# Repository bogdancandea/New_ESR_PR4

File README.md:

# New_ESR_PR4
A redesigned PCB for the original ESR-PR4 ESR meter

Back in 2023, my ESR-PR4 broke due to an error (I measured a charged capacitor). My first thought was: oh well, it served me well until now—I'll just get another one. Identical.
However, over the years, the manufacturer had stopped production, and even the website had disappeared.

With some information from specialized forums and with the help of https://web.archive.org, I managed to access an archived version of the website that used to sell the product:

https://web.archive.org/web/20180327142201/http://x-roast.home.ro/

At that time, the author had published both the schematic and the software written for the microcontroller. So I was able to repair my device by replacing and reprogramming the microcontroller.

That’s when I got the idea to republish the information. Since the original information did not include the PCB, I designed a PCB version so that electronics enthusiasts could build the device themselves.

The author of the schematic and the software is unknown to me. I am using and republishing this information because it was publicly available at x-roast.home.ro. I have no commercial interest whatsoever.

There is a mismatch between the original schematic and the HEX file: pins 10 and 11 of the microcontroller are swapped.
The first unit I built had a few errors, including the swapped pins 10 and 11, which were fixed by cutting PCB traces and soldering wires.

The published version has already been corrected.

A new, smaller PCB version is currently in development, which I will publish only after I have had the chance to test it.

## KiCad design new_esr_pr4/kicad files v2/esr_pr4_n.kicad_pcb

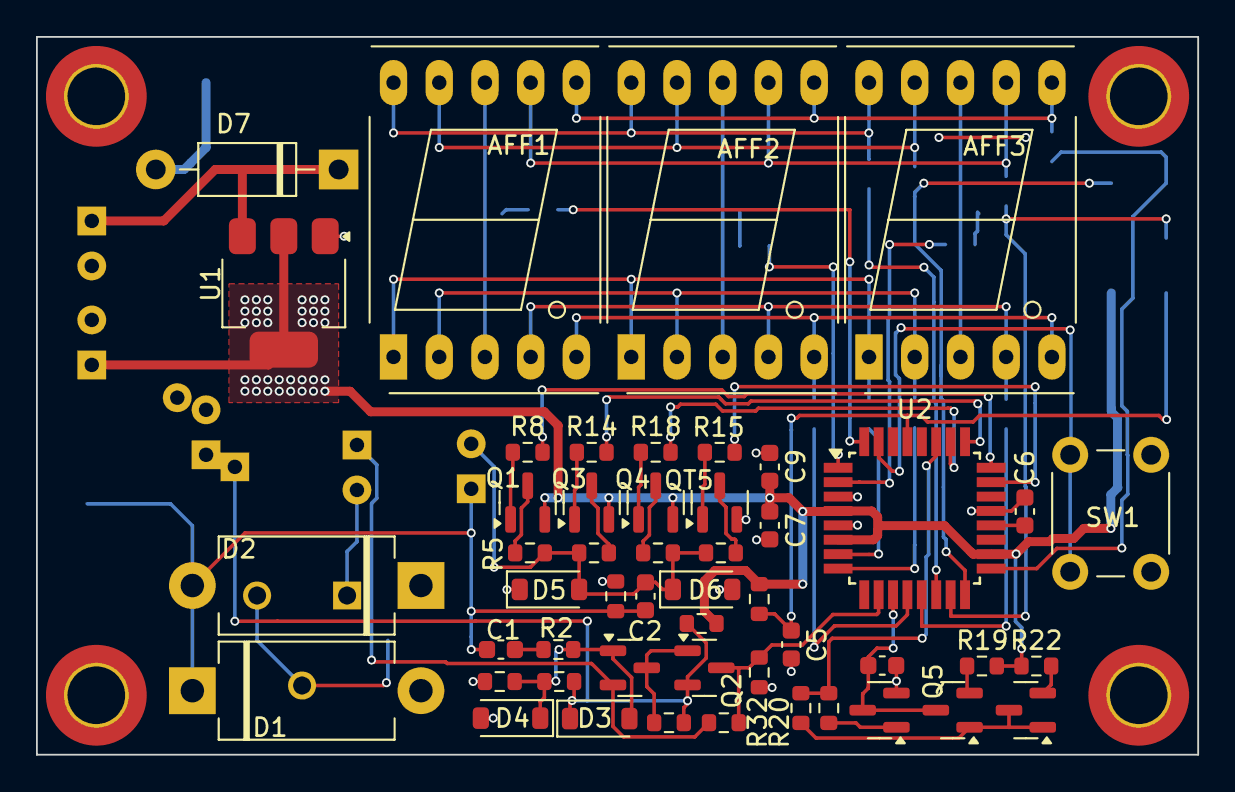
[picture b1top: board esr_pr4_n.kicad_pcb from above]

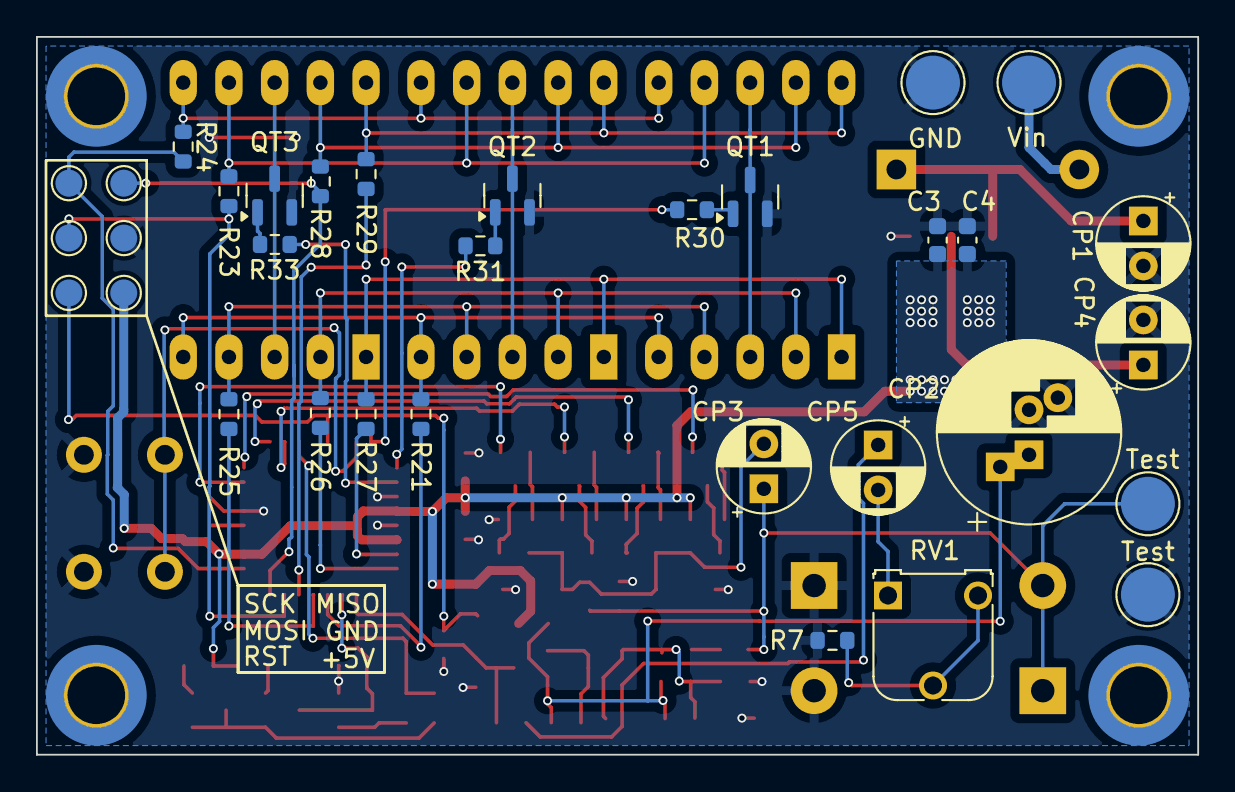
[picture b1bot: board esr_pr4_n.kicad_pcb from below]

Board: 2 copper layers, 64.5 x 39.9 mm, 87 parts (33 on the bottom side), 60 nets.

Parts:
+5V: ISP_5V; TestPoint_Pad_D1.5mm
AFF1, AFF2, AFF3: WL-T7DS; 7SegmentLED_LTS6760_LTS6780
C1: 33n; C_0603_1608Metric
C2, C5, C6, C7, C9: 100n; C_0603_1608Metric
C3: 1u/10V; C_0603_1608Metric
C4: 100n/10V; C_0603_1608Metric
C8: 470n; C_0603_1608Metric
CP1: 10u / 25V; CP_Radial_D5.0mm_P2.50mm
CP2: 100u; CP_Radial_D10.0mm_P2.50mm_P5.00mm
CP3, CP5: 22u; CP_Radial_D5.0mm_P2.50mm
CP4: 10u/10V; CP_Radial_D5.0mm_P2.50mm
D1, D2: 1N4007; D_DO-201_P12.70mm_Horizontal
D3, D4, D5, D6: 1N4148W; D_SOD-123
D7: 1N4007; D_DO-41_SOD81_P10.16mm_Horizontal
GND: GND; TestPoint_Pad_D3.0mm
GND#2: ISP_GND; TestPoint_Pad_D1.5mm
H1, H2, H3, H4: MountingHole; MountingHole_3.2mm_M3_DIN965_Pad_TopBottom
MISO: ISP_MISO; TestPoint_Pad_D1.5mm
MOSI: ISP_MOSI; TestPoint_Pad_D1.5mm
Q1, Q2, Q3, Q4, Q5, Q6: BC807; SOT-23
QT1, QT2, QT3, QT4, QT5, QT6: BC817; SOT-23
R1, R15, R16, R17, R19, R20, R22, R30, R31, R33: 10k; R_0603_1608Metric
R2, R10: 1k; R_0603_1608Metric
R3: 100k; R_0603_1608Metric
R4: 220k; R_0603_1608Metric
R5, R11: 100; R_0603_1608Metric
R6, R8, R14, R18: 2k2; R_0603_1608Metric
R7, R12: 220; R_0603_1608Metric
R9: 6k8; R_0603_1608Metric
R13: 680; R_0603_1608Metric
R21, R23, R24, R25, R26, R27, R28, R29: 470; R_0603_1608Metric
R32: 470k; R_0603_1608Metric
RST: ISP_RESET; TestPoint_Pad_D1.5mm
RV1: 200; Potentiometer_Runtron_RM-065_Vertical
SCK: ISP_SCK; TestPoint_Pad_D1.5mm
SW1: SW_Push; SW_PUSH_6mm
Test: Test+; TestPoint_Pad_D3.0mm
Test#2: Test-; TestPoint_Pad_D3.0mm
U1: AMS1117-5.0; SOT-223-3_TabPin2
U2: ATmega8L-8A; TQFP-32_7x7mm_P0.8mm
Vin: V_in; TestPoint_Pad_D3.0mm

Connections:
+5V: +5V.1, C3.1, C4.1, C7.2, C9.2, CP4.1, Q1.2 (E), Q3.2 (E), Q4.2 (E), R12.1, R17.1, R19.1, R22.1, U1.2 (VO), U2.4 (VCC), U2.6 (VCC), U2.18 (AVCC)
/constant current/cap_V: C8.1, Q5.3 (C), QT6.3 (C), U2.11 (PD7)
/constant current/discharge: R20.2, R32.2, U2.27 (PC4)
/display/C: R25.1, U2.13 (PB1)
/display/CK1: R30.2, U2.32 (PD2)
/display/CK2: R31.2, U2.1 (PD3)
/display/CK3: R33.2, U2.2 (PD4)
/display/D: R26.1, U2.8 (PB7/XTAL2)
/display/DP: R21.1, U2.12 (PB0)
/display/E: R27.1, U2.7 (PB6/XTAL1)
/display/G: R29.1, U2.14 (PB2)
/main/ADC_ESR: Q2.3 (C), R9.1, R13.1, U2.10 (PD6)
/main/HS1: R8.2, U2.24 (PC1)
/main/HS2: R14.2, U2.25 (PC2)
/main/HS3: R18.2, U2.26 (PC3)
/main/ISP_MISO: MISO.1, R28.1, U2.16 (PB4)
/main/ISP_MOSI: MOSI.1, R23.1, U2.15 (PB3)
/main/ISP_RESET: C5.1, R17.2, RST.1, U2.29 (PC6/~RESET)
/main/ISP_SCK: R24.1, SCK.1, U2.17 (PB5)
/main/LS1: R15.1, U2.23 (PC0)
/measurement circuit/pulse: C1.2, C2.2, CP3.1, D1.2 (A), D2.1 (K), R1.1, Test.1
GND: C3.2, C4.2, C5.2, C6.2, C7.1, C8.2, C9.1, CP1.2, CP2.2, CP4.2, D1.1 (K), D2.2 (A), D4.2 (A), D5.1 (K), D6.2 (A), GND.1, GND#2.1, QT1.2 (E), QT2.2 (E), QT3.2 (E), QT5.2 (E), QT6.2 (E), R1.2, R4.2, R7.2, R13.2, SW1.2, Test#2.1, U1.1 (GND), U2.3 (GND), U2.5 (GND), U2.21 (AGND)
unnamed: AFF1.5 (DP), AFF2.5 (DP), AFF3.5 (DP), R21.2
unnamed: AFF1.7 (a), AFF2.7 (a), AFF3.7 (a), R23.2
unnamed: AFF1.6 (b), AFF2.6 (b), AFF3.6 (b), R24.2
unnamed: AFF1.4 (c), AFF2.4 (c), AFF3.4 (c), R25.2
unnamed: AFF1.2 (d), AFF2.2 (d), AFF3.2 (d), R26.2
unnamed: AFF1.1 (e), AFF2.1 (e), AFF3.1 (e), R27.2
unnamed: AFF1.9 (f), AFF2.9 (f), AFF3.9 (f), R28.2
unnamed: AFF1.10 (g), AFF2.10 (g), AFF3.10 (g), R29.2
unnamed: C1.1, R2.2
unnamed: CP5.2, RV1.1
unnamed: D3.2 (A), D4.1 (K), QT4.1 (B), R2.1, R3.2, R4.1
unnamed: CP2.1, D3.1 (K), Q2.2 (E), R3.1, R6.1, R12.2
unnamed: C2.1, CP3.2, D5.2 (A), D6.1 (K), R5.2, R10.2, R11.1, R16.2
unnamed: D7.2 (A), Vin.1
unnamed: CP1.1, D7.1 (K), U1.3 (VI)
unnamed: Q1.1 (B), R8.1
unnamed: Q1.3 (C), R5.1
unnamed: Q2.1 (B), QT4.3 (C), R6.2
unnamed: Q3.1 (B), R14.1
unnamed: Q3.3 (C), R10.1
unnamed: Q4.1 (B), R18.1
unnamed: Q4.3 (C), R16.1
unnamed: Q5.1 (B), Q6.1 (B), Q6.3 (C), R32.1
unnamed: Q5.2 (E), R19.2
unnamed: Q6.2 (E), R22.2
unnamed: QT1.1 (B), R30.1
unnamed: AFF1.3 (C.A.), AFF1.8 (C.A.), QT1.3 (C)
unnamed: QT2.1 (B), R31.1
unnamed: AFF2.3 (C.A.), AFF2.8 (C.A.), QT2.3 (C)
unnamed: QT3.1 (B), R33.1
unnamed: AFF3.3 (C.A.), AFF3.8 (C.A.), QT3.3 (C)
unnamed: CP5.1, QT4.2 (E), R9.2
unnamed: QT5.1 (B), R15.2
unnamed: QT5.3 (C), R11.2
unnamed: QT6.1 (B), R20.1
unnamed: R7.1, RV1.2, RV1.3
unnamed: C6.1, U2.20 (AREF)
unnamed: SW1.1, U2.31 (PD1)
